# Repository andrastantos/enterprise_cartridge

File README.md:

A 512kB ROM cartridge design for the Enterprise computer
========================================================

This design can be used to add up to 512kB of ROM to the cartridge port of the Enterprise computers. Since the port
only exposes 16 address pins, 8 pages are selectable using jumpers.

You can read up on whole project in detail here: https://www.modularcircuits.com/blog/2025/02/25/enterprise-128-a-blast-from-the-past/

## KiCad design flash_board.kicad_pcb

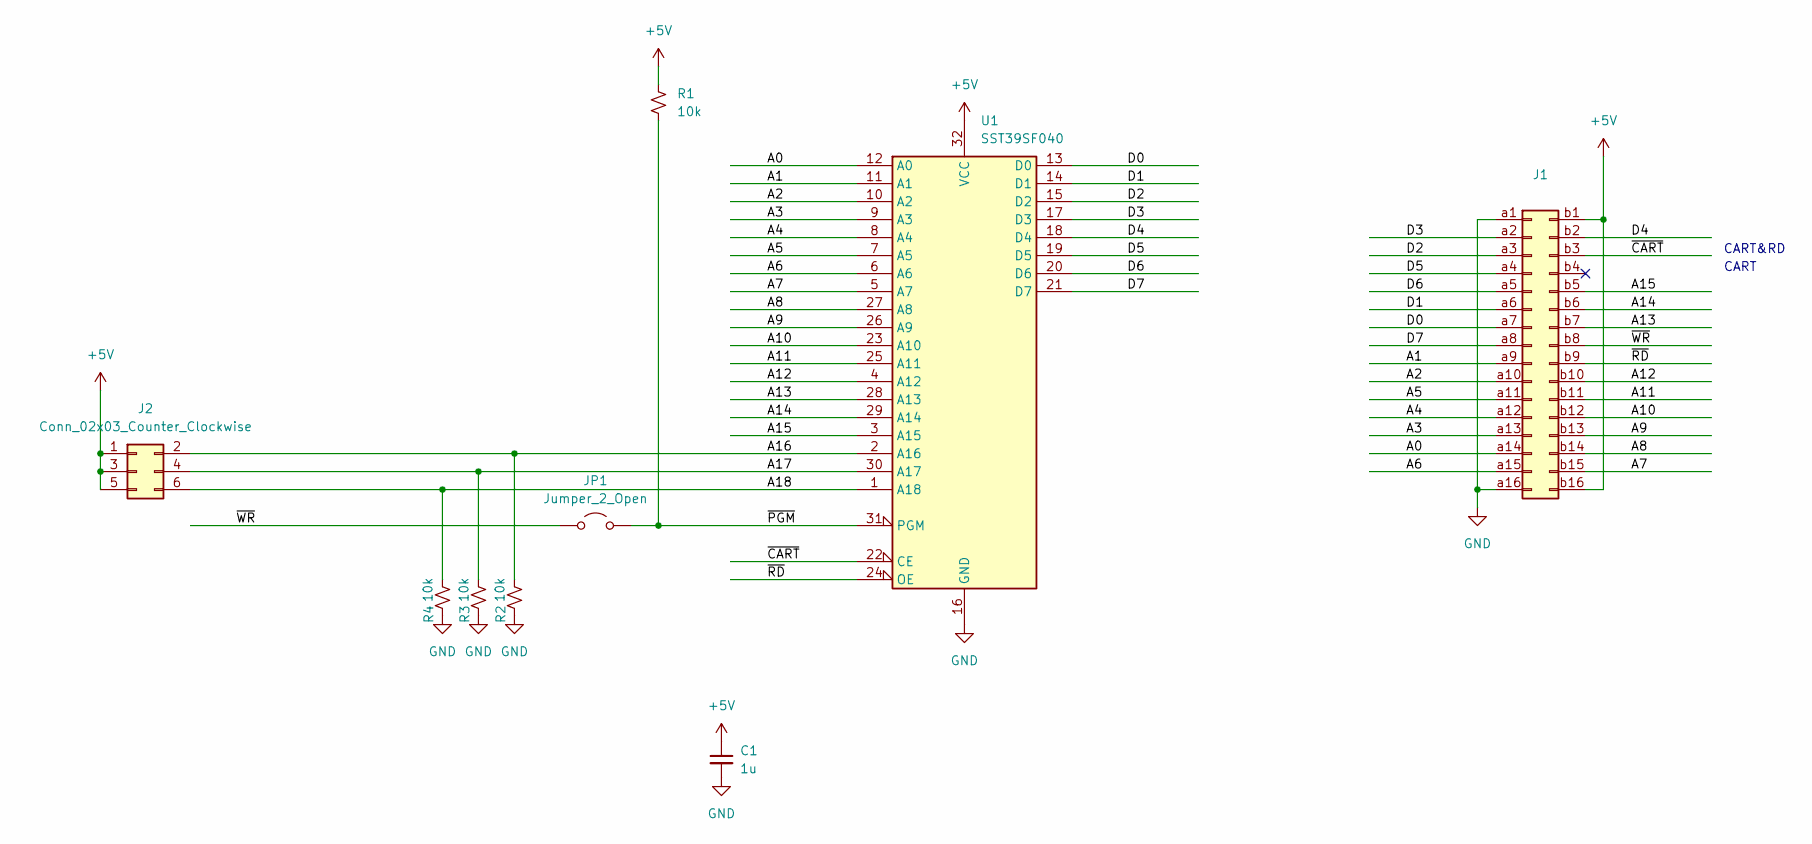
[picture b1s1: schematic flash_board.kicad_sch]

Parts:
C1: 1u; C_Disc_D3.0mm_W1.6mm_P2.50mm
J1: Conn_02x16_Row_Letter_First; ENTERPRISE_CARTRIGE_CONN
J2: Conn_02x03_Counter_Clockwise; PinHeader_2x03_P2.54mm_Vertical
JP1: Jumper_2_Open; PinHeader_1x02_P2.54mm_Vertical
R1, R2, R3, R4: 10k; R_Box_L8.4mm_W2.5mm_P5.08mm
U1: SST39SF040; DIP-32_W15.24mm_Socket_LongPads

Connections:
+5V: C1.1, J1.b1, J1.b16, J2.1, J2.3, J2.5, R1.1, U1.32 (VCC)
/A0: J1.a14, U1.12 (A0)
/A1: J1.a9, U1.11 (A1)
/A2: J1.a10, U1.10 (A2)
/A3: J1.a13, U1.9 (A3)
/A4: J1.a12, U1.8 (A4)
/A5: J1.a11, U1.7 (A5)
/A6: J1.a15, U1.6 (A6)
/A7: J1.b15, U1.5 (A7)
/A8: J1.b14, U1.27 (A8)
/A9: J1.b13, U1.26 (A9)
/A10: J1.b12, U1.23 (A10)
/A11: J1.b11, U1.25 (A11)
/A12: J1.b10, U1.4 (A12)
/A13: J1.b7, U1.28 (A13)
/A14: J1.b6, U1.29 (A14)
/A15: J1.b5, U1.3 (A15)
/A16: J2.2, R2.1, U1.2 (A16)
/A17: J2.4, R3.1, U1.30 (A17)
/A18: J2.6, R4.1, U1.1 (A18)
/D0: J1.a7, U1.13 (D0)
/D1: J1.a6, U1.14 (D1)
/D2: J1.a3, U1.15 (D2)
/D3: J1.a2, U1.17 (D3)
/D4: J1.b2, U1.18 (D4)
/D5: J1.a4, U1.19 (D5)
/D6: J1.a5, U1.20 (D6)
/D7: J1.a8, U1.21 (D7)
/~CART: J1.b3, U1.22 (CE)
/~PGM: JP1.2 (B), R1.2, U1.31 (PGM)
/~RD: J1.b9, U1.24 (OE)
/~WR: J1.b8, JP1.1 (A)
GND: C1.2, J1.a1, J1.a16, R2.2, R3.2, R4.2, U1.16 (GND)

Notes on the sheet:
CART
CART&RD

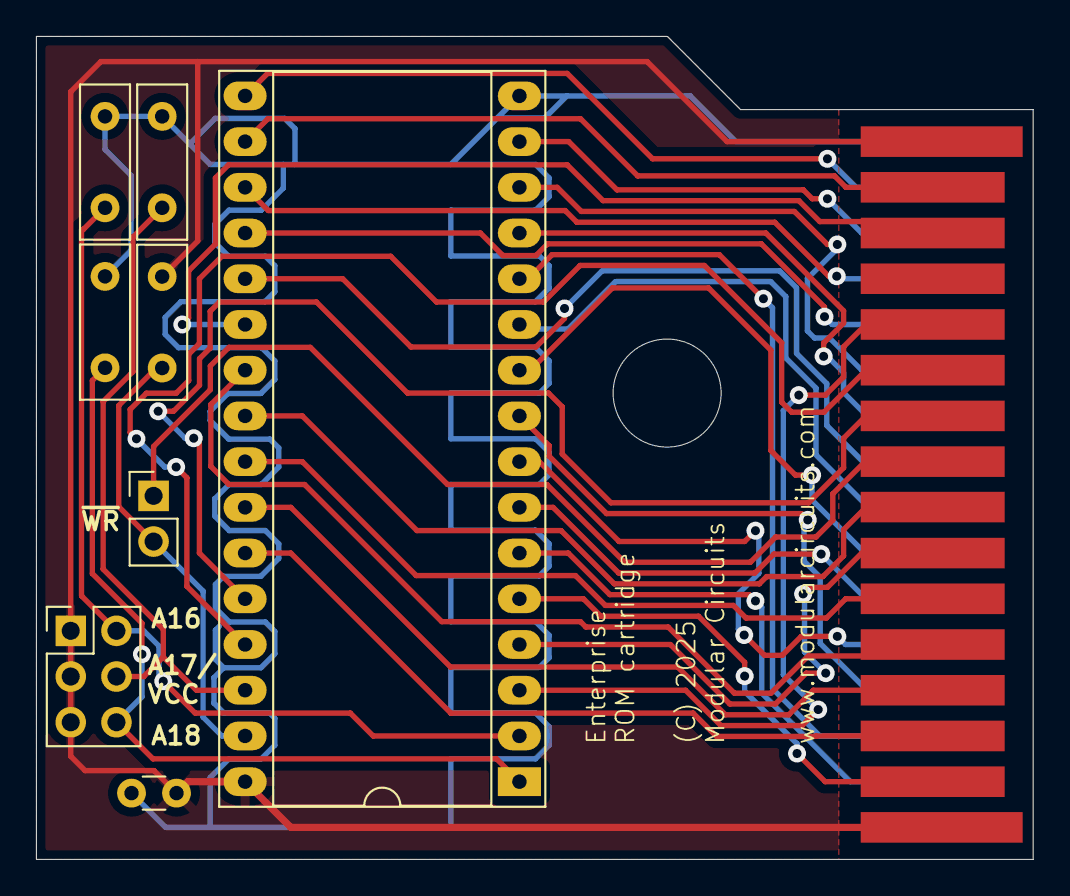
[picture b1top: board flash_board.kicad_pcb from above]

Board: 2 copper layers, 55.4 x 45.7 mm, 9 parts (0 on the bottom side), 33 nets.

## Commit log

2025-02-03 Updated board to hopefully final shape
2025-02-06 Resized board to stay flush with case
2025-02-06 Some small fixes and release package.
2025-02-07 Changed hole size to match 3D printed case model.
2025-02-23 Fixed D5 location on connector.
2025-02-25 Added README
2025-02-25 README changes.

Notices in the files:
flash_board.kicad_pcb:
(C) 2025
